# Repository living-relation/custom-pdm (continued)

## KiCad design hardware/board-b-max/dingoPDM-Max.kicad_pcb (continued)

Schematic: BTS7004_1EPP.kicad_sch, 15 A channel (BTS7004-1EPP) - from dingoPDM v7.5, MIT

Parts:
C47: 100nF; C_0805_2012Metric; MPN CC0805KRX7R9BB104; Digi-Key_PN 478-1395-1-ND
C51: 47nF; C_0805_2012Metric; MPN C0805C473K5RAC7800; Digi-Key_PN 399-C0805C473K5RACTUCT-ND
C55: 10nF; C_0805_2012Metric; MPN CL21B103KBANNNC; Digi-Key_PN 311-1136-1-ND
C59: 220pF; C_0805_2012Metric; MPN CC0805GRNPO0BN221; Digi-Key_PN 399-1138-1-ND
D21: 5.1V; D_SOD-323_HandSoldering; MPN PDZ5.1B,115; Digi-Key_PN 1727-5155-1-ND
D25: BYG23M; DO-214AC; MPN BYG23M-E3/TR; Digi-Key_PN BYG23M-E3/TR3GICT-ND
R56, R60, R68, R76: 4.7K; R_0805_2012Metric; MPN 0805W8F4701T5E; Digi-Key_PN 311-4.70KCRCT-ND
R64: 47R 1/4W; R_1206_3216Metric; MPN FRC1206J470 TS; Digi-Key_PN 311-47.0FRCT-ND
R72: 1.2K; R_0805_2012Metric; MPN 0805W8F1201T5E; Digi-Key_PN 311-1.20KCRCT-ND
U23: BTS7004-1EPP; TDSO-14; MPN BTS70041EPPXUMA1; LCSC C534825

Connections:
+12V: C47.2, C51.2, U23.15 (VS); also elsewhere on the board
/HighCurrentDrivers2/CH5/IS: C59.2, R68.1; also elsewhere on the board
GND: C47.1, C55.1, C59.1, D21.2 (A), D25.A, R64.1, R72.2; also elsewhere on the board
unnamed: D21.1 (K), R68.2, R76.1
unnamed: R60.1, U23.3 (DEN)
unnamed: C51.1, R64.2, U23.1 (GND)
unnamed: R56.1, U23.2 (IN)
unnamed: R72.1, R76.2, U23.4 (IS)
PF_DEN5_6: R60.2; also elsewhere on the board
PF_IN5: R56.2; also elsewhere on the board
PF_OUT5: C55.2, D25.K, U23.8 (OUT1), U23.9 (OUT2), U23.10 (OUT3), U23.11 (NC4), U23.12 (OUT4), U23.13 (OUT5), U23.14 (OUT6); also elsewhere on the board

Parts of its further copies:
C48, C49, C50: 100nF; C_0805_2012Metric; MPN CC0805KRX7R9BB104; Digi-Key_PN 478-1395-1-ND
C52, C53, C54: 47nF; C_0805_2012Metric; MPN C0805C473K5RAC7800; Digi-Key_PN 399-C0805C473K5RACTUCT-ND
C56, C57, C58: 10nF; C_0805_2012Metric; MPN CL21B103KBANNNC; Digi-Key_PN 311-1136-1-ND
C60, C61, C62: 220pF; C_0805_2012Metric; MPN CC0805GRNPO0BN221; Digi-Key_PN 399-1138-1-ND
D22, D23, D24: 5.1V; D_SOD-323_HandSoldering; MPN PDZ5.1B,115; Digi-Key_PN 1727-5155-1-ND
D26, D27, D28: BYG23M; DO-214AC; MPN BYG23M-E3/TR; Digi-Key_PN BYG23M-E3/TR3GICT-ND
R57, R58, R59, R61, R62, R63, R69, R70, R71, R77, R78, R79: 4.7K; R_0805_2012Metric; MPN 0805W8F4701T5E; Digi-Key_PN 311-4.70KCRCT-ND
R65, R66, R67: 47R 1/4W; R_1206_3216Metric; MPN FRC1206J470 TS; Digi-Key_PN 311-47.0FRCT-ND
R73, R74, R75: 1.2K; R_0805_2012Metric; MPN 0805W8F1201T5E; Digi-Key_PN 311-1.20KCRCT-ND
U24, U25, U26: BTS7004-1EPP; TDSO-14; MPN BTS70041EPPXUMA1; LCSC C534825

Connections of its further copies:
+12V: C48.2, C49.2, C50.2, C52.2, C53.2, C54.2, U24.15 (VS), U25.15 (VS), U26.15 (VS); also elsewhere on the board
/HighCurrentDrivers2/CH6/IS: C60.2, R69.1; also elsewhere on the board
/HighCurrentDrivers2/CH7/IS: C61.2, R70.1; also elsewhere on the board
/HighCurrentDrivers2/CH8/IS: C62.2, R71.1; also elsewhere on the board
GND: C48.1, C49.1, C50.1, C56.1, C57.1, C58.1, C60.1, C61.1, C62.1, D22.2 (A), D23.2 (A), D24.2 (A), D26.A, D27.A, D28.A, R65.1, R66.1, R67.1, R73.2, R74.2, R75.2; also elsewhere on the board
unnamed: D22.1 (K), R69.2, R77.1
unnamed: D23.1 (K), R70.2, R78.1
unnamed: D24.1 (K), R71.2, R79.1
unnamed: R61.1, U24.3 (DEN)
unnamed: C52.1, R65.2, U24.1 (GND)
unnamed: R57.1, U24.2 (IN)
unnamed: R73.1, R77.2, U24.4 (IS)
unnamed: R62.1, U25.3 (DEN)
unnamed: C53.1, R66.2, U25.1 (GND)
unnamed: R58.1, U25.2 (IN)
unnamed: R74.1, R78.2, U25.4 (IS)
unnamed: R63.1, U26.3 (DEN)
unnamed: C54.1, R67.2, U26.1 (GND)
unnamed: R59.1, U26.2 (IN)
unnamed: R75.1, R79.2, U26.4 (IS)
PF_DEN5_6: R61.2; also elsewhere on the board
PF_DEN7_8: R62.2, R63.2; also elsewhere on the board
PF_IN6: R57.2; also elsewhere on the board
PF_IN7: R58.2; also elsewhere on the board
PF_IN8: R59.2; also elsewhere on the board
PF_OUT6: C56.2, D26.K, U24.8 (OUT1), U24.9 (OUT2), U24.10 (OUT3), U24.11 (NC4), U24.12 (OUT4), U24.13 (OUT5), U24.14 (OUT6); also elsewhere on the board
PF_OUT7: C57.2, D27.K, U25.8 (OUT1), U25.9 (OUT2), U25.10 (OUT3), U25.11 (NC4), U25.12 (OUT4), U25.13 (OUT5), U25.14 (OUT6); also elsewhere on the board
PF_OUT8: C58.2, D28.K, U26.8 (OUT1), U26.9 (OUT2), U26.10 (OUT3), U26.11 (NC4), U26.12 (OUT4), U26.13 (OUT5), U26.14 (OUT6); also elsewhere on the board

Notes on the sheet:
RC Filter
Flyback

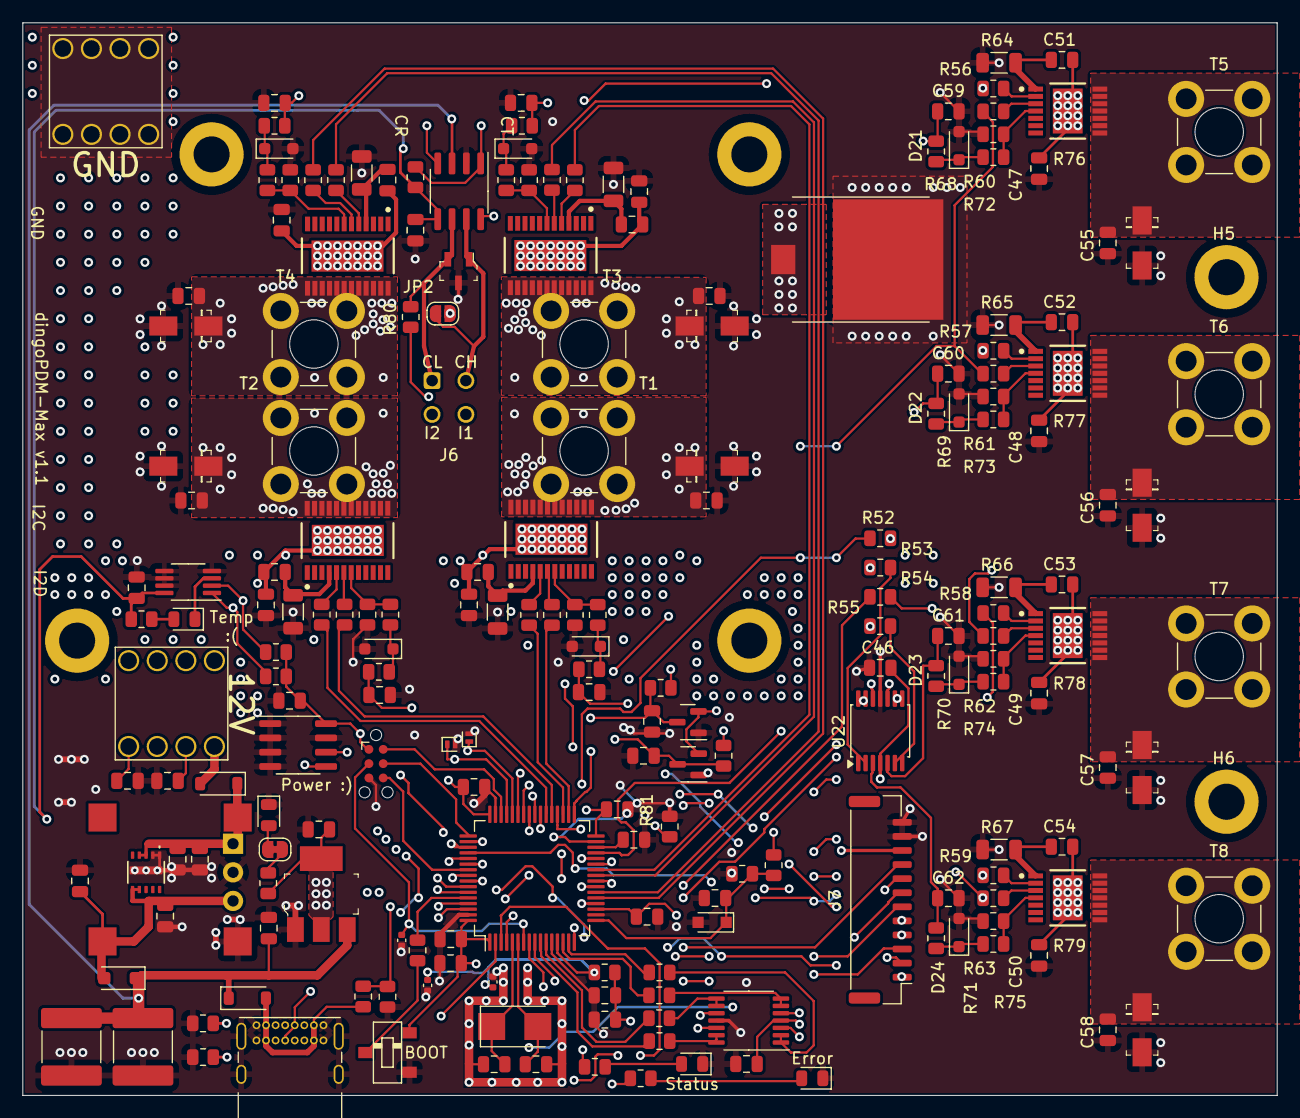
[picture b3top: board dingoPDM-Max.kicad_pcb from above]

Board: 4 copper layers, 111.4 x 95.2 mm, 211 parts (1 on the bottom side), 139 nets.

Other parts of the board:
H5, H6: M3; MountingHole_3.2mm_M3_ISO7380_Pad

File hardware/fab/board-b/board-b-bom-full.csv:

Qty,Designator,Value,Footprint,Manufacturer,MPN,LCSC,Digi-Key,Approved alternates,Fitted by
20,"C1,C2,C5,C9,C11,C12,C13,C14,C16,C18,C22,C24,C28,C32,C36,C46,C47,C48,C49,C50",100nF,C_0805_2012Metric,YAGEO,CC0805KRX7R9BB104,C49678,478-1395-1-ND,,JLCPCB SMT
3,"C3,C66,C67",4.7uF,C_0805_2012Metric,TDK,CGA4J1X7R1H475KT0Y0N,C694229,,"HRE CGA0805X7R475K500MT (4.7 uF 50 V X7R 0805, LCSC C6119944)",JLCPCB SMT
2,"C4,C68",22uF,C_0805_2012Metric,Murata,GRM21BZ71A226ME15L,C907991,,"CCTC TCC0805X7R226M100FT (22 uF 10 V X7R 0805, LCSC C53133025)",JLCPCB SMT
1,C6,10uF,C_0805_2012Metric,Samsung Electro-Mechanics,CL21B106KPQNNNE,C32635,,,JLCPCB SMT
2,"C7,C8",27pF,C_0805_2012Metric,FH (Guangdong Fenghua),0805CG270J500NT,C1808,478-10518-1-ND,,JLCPCB SMT
2,"C10,C15",4.7uF,C_0805_2012Metric,Samsung Electro-Mechanics,CL21B475KAFNNNE,C98195,,,JLCPCB SMT
2,"C17,C19",1uF,C_0805_2012Metric,Samsung Electro-Mechanics,CL21B105KBFNNNE,C28323,311-1365-1-ND,,JLCPCB SMT
10,"C20,C21,C25,C29,C33,C37,C55,C56,C57,C58",10nF,C_0805_2012Metric,Samsung Electro-Mechanics,CL21B103KBANNNC,C1710,311-1136-1-ND,,JLCPCB SMT
8,"C23,C27,C31,C35,C51,C52,C53,C54",47nF,C_0805_2012Metric,KEMET,C0805C473K5RAC7800,C3879816,399-C0805C473K5RACTUCT-ND,"KEMET C0805C473K5RACTU (same part, other reel code; DK 399-C0805C473K5RACTUCT-ND)",JLCPCB SMT
8,"C26,C30,C34,C38,C59,C60,C61,C62",220pF,C_0805_2012Metric,YAGEO,CC0805GRNPO0BN221,C576920,399-1138-1-ND,,JLCPCB SMT
2,"C39,C40",47uF,C_2220_5750Metric,PSA,FS55X476K250LRG,C22388555,445-7935-1-ND,,JLCPCB SMT
2,"C63,C65",100nF,C_0402_1005Metric,Samsung Electro-Mechanics,CL05B104KO5NNNC,C1525,,YAGEO CC0402KRX7R7BB104 (X7R 16 V 0402),JLCPCB SMT
1,C64,1uF,C_0402_1005Metric,CCTC,TCC0402X7R105K100AT,C47325373,,"YAGEO CC0402KRX7R6BB105 (X7R 10 V 0402, LCSC C7500381)",JLCPCB SMT
1,D1,3.3V,D_SOD-323_HandSoldering,Nexperia,"PDZ3.3B,115",C426855,1727-5150-1-ND,,JLCPCB SMT
1,D2,SM8S24CA,D_DO-218AB_Vishay_SM8S,Bourns,SM8S24CA-Q,C1976790,SM8S24CA-QCT-ND,"Vishay SM8S24CAHM3/I (LCSC C20036943, DK 112-SM8S24CAHM3/ITR-ND); Panjit SM8H24CAS-AU",JLCPCB SMT
2,"D3,D6",Schottky,D_SOD-123,Nexperia,PMEG10010ELRX,C179426,1727-2394-1-ND,,JLCPCB SMT
1,D4,PMEG2010AEH,D_SOD-123F,Nexperia,"PMEG2010AEH,115",C110921,"1727-PMEG2010AEH,115CT-ND",,JLCPCB SMT
1,D5,GRN,LED_0805_2012Metric,OSRAM,LG R971-KN-1-0-20-R18,C2899888,475-1410-1-ND,,do not fit
2,"D7,D10",RED,LED_0805_2012Metric,OSRAM,LS R976-NR-1-0-20-R18,C2899997,475-1278-1-ND,,JLCPCB SMT
1,D8,GRN,LED_0805_2012Metric,OSRAM,LG R971-KN-1-0-20-R18,C2899888,475-1410-1-ND,,JLCPCB SMT
1,D9,NUP2105LT1G,SOT-23-3,DOWO,NUP2105LT1G,C2976509,NUP2105LT1GOSCT-ND,onsemi NUP2105LT1G (DK NUP2105LT1GOSCT-ND),JLCPCB SMT
2,"D11,D12",BAT54S,SOT-23,Nexperia,"BAT54S,215",C47546,BAT54SLT1GOSCT-ND,onsemi BAT54SLT1G (DK BAT54SLT1GOSCT-ND),JLCPCB SMT
8,"D13,D15,D17,D19,D25,D26,D27,D28",BYG23M,DO-214AC,Vishay,BYG23M-E3/TR,C141573,BYG23M-E3/TR3GICT-ND,,JLCPCB SMT
8,"D14,D16,D18,D20,D21,D22,D23,D24",5.1V,D_SOD-323_HandSoldering,Nexperia,"PDZ5.1B,115",C85392,1727-5155-1-ND,,JLCPCB SMT
2,"D29,D30",PESD5V0F1BL,D_SOD-882,Nexperia,"PESD5V0F1BL,315",C45961,,Nexperia PESD5V0F1BLZ (LCSC C6952437); BORN PESD5V0F1BL-N (LCSC C2929237),JLCPCB SMT
1,FB1,Ferrite_Bead_Small,R_0805_2012Metric,Murata,BLM21PG221SN1D,C85840,490-1054-1-ND,,JLCPCB SMT
2,"J1,J3",RedCubeTerminal,M6_Hole_8Pin_7461084,Wurth Elektronik,7461084,C6828431,732-3203-ND,,not JLCPCB: press in after delivery (fab-notes.md)
1,J2,USB_C_Receptacle_USB2.0,USB_C_Receptacle_GCT_USB4085,GCT,USB4085-GF-A,C7095263,2073-USB4085-GF-ACT-ND,,JLCPCB THT
1,J7,INPUT BOARD B_IN3-10,JST_GH_BM12B-GHS-TBT_1x12-1MP_P1.25mm_Vertical,JST,BM12B-GHS-TBT,C20089173,455-BM12B-GHS-TBTCT-ND,,JLCPCB SMT
1,R1,47K,R_0805_2012Metric,YAGEO,RT0805DRD0747KL,C327035,311-47.0KCRCT-ND,"UNI-ROYAL 0805W8F4702T5E (1 %, LCSC C17713, basic)",JLCPCB SMT
36,"R2,R4,R15,R16,R21,R22,R25,R26,R27,R28,R31,R32,R33,R34,R37,R38,R39,R40,R43,R44,R56,R57,R58,R59,R60,R61,R62,R63,R68,R69,R70,R71,R76,R77,R78,R79",4.7K,R_0805_2012Metric,UNI-ROYAL,0805W8F4701T5E,C17673,311-4.70KCRCT-ND,,JLCPCB SMT
1,R3,120R,R_0805_2012Metric,UNI-ROYAL,0805W8F1200T5E,C17437,311-120CRCT-ND,YAGEO RC0805FR-07120RL (DK 311-120CRCT-ND),do not fit
5,"R5,R10,R12,R13,R81",10K,R_0805_2012Metric,UNI-ROYAL,0805W8F1002T5E,C17414,311-10.0KCRDKR-ND,,JLCPCB SMT
2,"R6,R7",5.1K,R_0805_2012Metric,Viking,ARG05FTC5101,C218638,311-5.1KARCT-ND,,JLCPCB SMT
12,"R8,R9,R14,R17,R18,R19,R20,R52,R53,R54,R55,R80",120R,R_0805_2012Metric,UNI-ROYAL,0805W8F1200T5E,C17437,311-120CRCT-ND,YAGEO RC0805FR-07120RL (DK 311-120CRCT-ND),JLCPCB SMT
1,R11,1K,R_0805_2012Metric,UNI-ROYAL,0805W8F1001T5E,C17513,311-1.0KARCT-ND,,JLCPCB SMT
8,"R23,R29,R35,R41,R72,R73,R74,R75",1.2K,R_0805_2012Metric,UNI-ROYAL,0805W8F1201T5E,C17379,311-1.20KCRCT-ND,YAGEO RC0805FR-071K2L (DK 311-1.20KCRCT-ND),JLCPCB SMT
8,"R24,R30,R36,R42,R64,R65,R66,R67",47R 1/4W,R_1206_3216Metric,FOJAN,FRC1206J470 TS,C2907508,311-47.0FRCT-ND,,JLCPCB SMT
1,SW1,BOOT,CJS-1200TB,Nidec Components,CJS-1200TB1,C2921631,563-CJS-1200TB1CT-ND,,JLCPCB SMT
8,"T1,T2,T3,T4,T5,T6,T7,T8",74650074R,Wuerth_REDCUBE-THR_WP-THRBU_74650074_THR,Wurth Elektronik,74650074R,(none: JLCPCB global sourcing by MPN),732-74650074RCT-ND,,JLCPCB THT
1,U1,VXO780x-500-M,VXO78x-500-M,CUI,VXO7805-500-M-TR,C5137464,102-VXO7805-500-M-CT-ND,,do not fit
1,U2,TLV1117LV33DCYR,SOT-223,Texas Instruments,TLV1117LV33DCYR,C15578,296-28778-1-ND,,JLCPCB SMT
1,U3,MCP2562FD-E/SN,SOIC-8_3.9x4.9mm_P1.27mm,Microchip,MCP2562FD-E/SN,C124016,MCP2562FD-E/SN-ND,,JLCPCB SMT
1,U4,STM32F446RET7,LQFP-64_10x10mm_P0.5mm,STMicroelectronics,STM32F446RET7,C1343794,497-16775-ND,STMicroelectronics STM32F446RET6 (s9a; LCSC C69336),JLCPCB SMT
1,U5,CY15B064J-SXE,SOIC-8_3.9x4.9mm_P1.27mm,Infineon,CY15B064J-SXE,C2953601,448-CY15B064J-SXE-ND,"RAMXEED MB85RC64TAPNF-G-AWERE2 (LCSC C43379785; 105 C part: fit only with the board's critical limit keeping the FRAM <= 105 C, docs/heat-analysis.md 5)",JLCPCB SMT
1,U6,MCP9808,MSOP-8_3x3mm_P0.65mm,Microchip,MCP9808T-E/MS,C129490,MCP9808T-E/MSCT-ND,,JLCPCB SMT
2,"U7,U22",TLV9004IPWR,TSSOP-14_4.4x5mm_P0.65mm,Texas Instruments,TLV9004IPWR,C2058050,296-51827-1-ND,"Microchip MCP6004T-E/ST (RRIO, -40 to 125 C, same TSSOP-14 pinout, DS20001733)",JLCPCB SMT
4,"U8,U9,U10,U11",BTS70012-1ESP,TSDSO-24,Infineon,BTS700121ESPXUMA1,C3232444,448-BTS700121ESPXUMA2CT-ND,Infineon BTS700121ESPXUMA2 (DK 448-BTS700121ESPXUMA2CT-ND),JLCPCB SMT
1,U12,OKI-78SR-5_1.5-W36H-C,Converter_DCDC_Murata_OKI-78SR_Horizontal,Murata,OKI-78SR-5/1.5-W36H-C,C266374,811-2692-ND,,do not fit
4,"U23,U24,U25,U26",BTS7004-1EPP,TDSO-14,Infineon,BTS70041EPPXUMA1,C534825,BTS70041EPPXUMA1CT-ND,,JLCPCB SMT
1,U27,LMZM23601V5,Texas_SIL0010A_MicroSiP-10-1EP_3.8x3mm_P0.6mm_EP0.7x2.9mm_TI,Texas Instruments,LMZM23601V5SILR,C2868357,296-LMZM23601V5SILRCT-ND,"TI LMZM23601V5SILT (same part, 250 reel, LCSC C2876787)",JLCPCB SMT
1,Y1,8MHz,Crystal_SMD_5032-2Pin_5.0x3.2mm_HandSoldering,ECS Inc.,ECS-80-18-30Q-CES-TR,(none: JLCPCB global sourcing by MPN),50-ECS-80-18-30Q-CES-TRCT-ND,"ECS ECS-80-18-30Q-VY-TR (-40..105 C, LCSC C6844210)",JLCPCB SMT

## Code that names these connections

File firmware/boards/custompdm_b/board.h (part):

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/*
 * GPIOA setup:
 *
 * PA0  - PF3_IS                    (analog in).
 * PA1  - PF4_IS                    (analog in).
 * PA2  -                           (input pullup).
 * PA3  - BATT_SENSE                (analog in).
 * PA4  -                           (input pullup).
 * PA5  - PF4_DEN                   (output pushpull pulldown).
 * PA6  - PF4_IN                    (output pushpull pulldown).
 * PA7  -                           (input pullup).
 * PA8  -                           (input pullup).
 * PA9  - USB_VBUS                  (input pulldown).
 * PA10 - DIG_IN1                   (input).
 * PA11 - USB_DM                    (alternate 10, usb dm).
 * PA12 - USB_DP                    (alternate 10, usb dp).
 * PA13 - SWDIO                     (alternate 0, swdio).
 * PA14 - SWCLK                     (alternate 0, swclk).
 * PA15 -                           (input pullup).
 */
#define VAL_GPIOA_MODER             (PIN_MODE_ANALOG(GPIOA_PIN0) |          \
                                     PIN_MODE_ANALOG(GPIOA_PIN1) |          \
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/*
 * GPIOB setup:
 *
 * PB0  - PF3_IN                    (output pushpull puLLdown).
 * PB1  -                           (input pullup).
 * PB2  -                           (input pullup).
 * PB3  - SWO                       (alternate 0, swo).
 * PB4  -                           (input pullup).
 * PB5  -                           (input pullup).
 * PB6  - I2C1_SCL                  (alternate 4, i2c scl).
 * PB7  - I2C1_SDA                  (alternate 4, i2c sda).
 * PB8  - CAN_RX                    (alternate 9, can rx).
 * PB9  - CAN_TX                    (alternate 9, can tx).
 * PB10 -                           (input pullup).
 * PB11 -                           (input pullup).
 * PB12 -                           (input pullup).
 * PB13 - PF1_DEN                   (output pushpull pulldown).
 * PB14 - PF1_IN                    (output pushpull pulldown).
 * PB15 -                           (input pullup).
 */
#define VAL_GPIOB_MODER             (PIN_MODE_OUTPUT(GPIOB_PIN0) |          \
                                     PIN_MODE_ANALOG(GPIOB_PIN1) |           \
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/*
 * GPIOC setup:
 *
 * PC0  - ERROR_LED                 (output pushpull pulldown).
 * PC1  - STATUS_LED                (output pushpull pulldown).
 * PC2  - PF2_IS                    (analog input).
 * PC3  - PF1_IS                    (analog input).
 * PC4  -                           (input pullup).
 * PC5  - PF3_DEN                   (output pushpull pulldown).
 * PC6  - PF2_DEN                   (output pushpull pulldown).
 * PC7  - PF2_IN                    (output pushpull pulldown).
 * PC8  -                           (input pullup).
 * PC9  - DIG_IN2                   (input).
 * PC10 - E1                        (output pushpull pulldown).
 * PC11 - E2                        (output pushpull pulldown).
 * PC12 - CAN_STANDBY               (output pushpull pulldown).
 * PC13 - E3                        (output pushpull pulldown).
 * PC14 -                           (input pullup).
 * PC15 -                           (input pullup).
 */
#define VAL_GPIOC_MODER             (PIN_MODE_OUTPUT(GPIOC_PIN0) |          \
                                     PIN_MODE_OUTPUT(GPIOC_PIN1) |          \
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 *
 * PD0  - PIN0                      (input pullup).
 * PD1  - PIN1                      (input pullup).
 * PD2  - PIN2                      (input pullup).
 * PD3  - PIN3                      (input pullup).
 * PD4  - PIN4                      (input pullup).
 * PD5  - PIN5                      (input pullup).
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/*
 * GPIOH setup:
 *
 * PH0  - PIN0                      (input pullup).
 * PH1  - PIN1                      (input pullup).
 * PH2  - PIN2                      (input pullup).
 * PH3  - PIN3                      (input pullup).
 * PH4  - PIN4                      (input pullup).
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
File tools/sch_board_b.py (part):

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  * HighCurrentDrivers2.kicad_sch - copy of the Max's HighCurrentDrivers page (4 channel sheets + LM324 IS buffer),
                              pointed at BTS7004_1EPP and renamed to channels 5-8. Channels 5+6 and 7+8 share a DEN pin.
  * MCU pins (were no-connect):
        PF_IN5 PA8 (TIM1_CH1)   PF_IN6 PB10 (TIM2_CH3)   PF_IN7 PA15 (TIM2_CH1)   PF_IN8 PC8 (TIM8_CH3)
        PF_DEN5_6 PB12          PF_DEN7_8 PB15
        PF_IS5 PA2 (ADC_IN2)    PF_IS6 PA4 (ADC_IN4)     PF_IS7 PA7 (ADC_IN7)     PF_IS8 PC4 (ADC_IN14)
        B_IN3..B_IN10 = PC14 PC15 PC13 PD2 PB4 PB5 PC10 PC11       B_AN = PB1 (ADC_IN9)
        (B_IN5 is on PC13, not PB2: PB2 is BOOT1, a start-up pin. Dan, 2026-11-10, B1. PB2 stays no-connect.)
  * Connectors sheet: T1-T8 = bolt-down output terminals (Wuerth REDCUBE THR M4), one per output; J4 (Deutsch DT) removed.
                      J6 = wire pads in the Micro-Fit 2x2 hole pattern (a2b, 2026-11-12): 1 CAN_L, 2 CAN_H, 3 INPUT2,
                      4 INPUT1 (order follows the old J4 track ends).
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GH12 = "Connector_JST:JST_GH_BM12B-GHS-TBT_1x12-1MP_P1.25mm_Vertical"    # top entry: sits inside the board, not at an edge

OUT_PINS = {  # net: (U4 pin name, shape)
    "PF_IN5": ("PA8", "output"), "PF_IN6": ("PB10", "output"), "PF_IN7": ("PA15", "output"), "PF_IN8": ("PC8", "output"),
    "PF_DEN5_6": ("PB12", "output"), "PF_DEN7_8": ("PB15", "output"),
    "PF_IS5": ("PA2", "input"), "PF_IS6": ("PA4", "input"), "PF_IS7": ("PA7", "input"), "PF_IS8": ("PC4", "input"),
}
IN_PINS = {"B_IN3": "PC14", "B_IN4": "PC15", "B_IN5": "PC13", "B_IN6": "PD2", "B_IN7": "PB4", "B_IN8": "PB5",
           "B_IN9": "PC10", "B_IN10": "PC11", "B_AN": "PB1"}
RENAME_HCD2 = {"PF_IN1": "PF_IN5", "PF_IN2": "PF_IN6", "PF_IN3": "PF_IN7", "PF_IN4": "PF_IN8",
               "PF_DEN1": "PF_DEN5_6", "PF_DEN2": "PF_DEN5_6", "PF_DEN3": "PF_DEN7_8", "PF_DEN4": "PF_DEN7_8",
               "PF_IS1": "PF_IS5", "PF_IS2": "PF_IS6", "PF_IS3": "PF_IS7", "PF_IS4": "PF_IS8",
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    x, y = pin_at(pin)
    t = drop_nc(t, x, y)
    items.append(glabel(net, x, y, x > X, shape))
# test points: the PC10 / PC11 / PC13 points become input labels (their wires stay), every test point is removed
TP_OF = {"PC10": "TP4", "PC11": "TP3", "PC13": "TP2"}
tp_at = {}
for s2, e2 in top_blocks(t, "symbol"):
    bb = t[s2:e2]
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wr("MCU.kicad_sch", t)

removed, dropped_labels = [], []
KEEP = set(IN_PINS)                       # our new labels sit on the PC10/PC11 test point spots
for f in sorted(glob.glob("*.kicad_sch")):
    x = rd(f)
    spots = []
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        continue
    out.append(x[pos:])
    x = "".join(out)
    # labels that only marked a test point pin (CAN_TX/RX, I2C) would dangle: drop them
    for head in ("label", "global_label"):
        out, pos = [], 0
        for s2, e2 in top_blocks(x, head):
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                pos = e2
    out.append(x[pos:])
    x = "".join(out)
    # PC13 (TP2), only when PC13 is not used as an input: remove the wire run from the test point back to the U4 pin
    # and flag the pin no-connect
    for r, p in spots:
        if r != "TP2" or f != "MCU.kicad_sch" or "PC13" in IN_PINS.values():
            continue
        ends = set(pin_end.values())
        cur, gone = p, []
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                    if abs(a[0] - cur[0]) < .01 and abs(a[1] - cur[1]) < .01:
                        hits.append(((s2, e2), b2))
            if len(hits) != 1:
                raise SystemExit(f"PC13 wire walk: {len(hits)} wires at {cur}")
            gone.append(hits[0][0])
            cur = hits[0][1]
            if any(abs(cur[0] - a) < .01 and abs(cur[1] - b2) < .01 for a, b2 in ends):
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        for s2, e2 in sorted(gone, reverse=True):
            x = x[:s2 - 2] + x[e2:]
        x = insert_items(x, [f'(no_connect\n\t\t(at {fmt(cur[0])} {fmt(cur[1])})\n\t\t(uuid "{u()}")\n\t)'])
        print("PC13 test point wiring removed:", len(gone), "wires; pin flagged no-connect at", cur)
    wr(f, x)
print("test points removed:", removed, "labels dropped:", dropped_labels)

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J4_AT = tuple(map(float, re.search(r"\(at ([\d.\-]+) ([\d.\-]+)", j4).groups()))
SHEET_PATH = re.search(r'\(path "([^"]+)"', j4).group(1)
c_glab = {re.search(r'\(global_label "([^"]+)"', t[s2:e2]).group(1): t[s2:e2] for s2, e2 in top_blocks(t, "global_label")}
tpl = c_glab["PF_OUT1"]                         # angle 180, left of the connector pins
s1, e1 = symbol_by_ref(t, "J1")
j1 = t[s1:e1]                                   # RedCube terminal symbol (1 pin), rotated 270: pin end 3.81 above the origin
if not re.search(r"\(at [\d.\-]+ [\d.\-]+ 270\)", j1):
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
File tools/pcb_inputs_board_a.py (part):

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
1. J6 placed at the left board edge (free 6.9 x 19.8 mm spot), plug opening facing the edge, linked to its
   schematic symbol (path from the netlist) so DRC schematic parity holds.
2. Pad nets from the netlist. R12 set DNP (cuts the unused IS2 buffer off PC2 / PF_IS2).
3. GND pins 11-12: short stub + via into the In1 GND plane.
4. Signals and +3V3 routed by route_board_a's A* router, preferring In2 (no planes there).
"""
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
# ---- 4. routes
R.setup(b, WIN, {"F.Cu": 1.6, "In2.Cu": 1.0, "B.Cu": 2.5})
# IN_3..IN_7 = PC10, PC11, PB4, PC13, PB3 (ex-SWO)
U4 = {f"/MCU/IN_{k}": pin for k, pin in zip(range(3, 8), ("51", "52", "56", "2", "55"))}
U4["PF_IS2"] = "10"
for num, net in list(SIG.items()) + [("9", "PF_IS2")]:
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

# ---- 5. free the spare U4 pins, step by step
# PC10, PC11, PC13 already run out to the old expansion test pads (TP8-TP10, now removed): route from those ends.
# PB3 (ex-SWO) runs out to the Tag-Connect J4: cut the last piece at J4 and route from the cut end.
# The rest fan out; a few slow-signal blockers are ripped up first and reconnected after. Plane nets (GND, +3V3,
# +12V) and the crystal are never ripped.
import pcb_rework as RW
EXISTING = ["/MCU/IN_3", "/MCU/IN_4", "/MCU/IN_6", "/MCU/IN_7"]
# Only PB4 needs a fan-out, and it escapes without ripping anything. (Experiments 2026-11-08: freeing PB5, PD2,
# PB13 or PA15 boxes in CAN_STANDBY, I2C or PF_DSEL3_4, which then can't reconnect, even with 0.6/0.3 vias.)
# Format kept for later boards: "refan" = ripped nets re-fanned first, "sides" = fan-out direction limits.
STEPS = [
    {"targets": ["/MCU/IN_5"], "rip": []},                                     # PB4
]
escape = {}
doomed = [f for f in b.GetFootprints() if f.GetReference().startswith("TP")]
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
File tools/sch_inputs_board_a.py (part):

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Run from hardware/board-a after sch_swap_board_a.py / sch_repin_board_a.py. Edits files in place.

J6 pinout (to the input daughter board):
  1-5  IN_3..IN_7 -> PC10, PC11, PB4, PC13, PB3 (5 new inputs: the most that escape U4 without disturbing dingo's
       own signals). PC10/PC11/PC13 were dingo's expansion test points E1-E3 (TP8-TP10, removed); PB3 was SWO
       (trace output, not needed to program/debug; the Tag-Connect pin is left unused); PB4 was no-connect.
  6-8  not connected (kept so one input board design also fits board B, which has more spare pins)
  9    PF2_IS (PC2, spare analog; R12 set DNP so the unused IS2 buffer no longer drives it)
  10   +3V3 (pull-up supply for the input board DIP switches)
  11-12 GND
"""
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#   ("tp", ref, name)            test point symbol -> label at its pin (the wire to U4 stays)
#   ("relabel", (x, y), name)    existing local label renamed
MCU_PINS = [
    ("tp", "TP8", "IN_3"),                        # PC10 pin 51 (was E1)
    ("tp", "TP9", "IN_4"),                        # PC11 pin 52 (was E2)
    ("nc", (127.0, 90.805), "IN_5", "R"),         # PB4  pin 56
    ("tp", "TP10", "IN_6"),                       # PC13 pin 2 (was E3)
    ("relabel", (138.43, 88.265), "IN_7"),        # PB3  pin 55 (was SWO)
]
N_IN = len(MCU_PINS)                              # J6 pins 1..N_IN carry IN_3..; the rest up to 8 are not connected
SWO_TAG_SIDE = (38.1, 172.72)                     # SWO label at the Tag-Connect (J4) -> renamed SWO_UNUSED
TESTPOINT_LIB = "Connector:TestPoint"             # every test point on every sheet is removed (Dan, 2026-11-08)
PWR_REFS = ["#PWR122", "#PWR123", "#PWR124"]

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    f'(pin "{n}"\n\t\t\t(uuid "{u()}")\n\t\t)' for n in range(1, 13)), j, count=1)
j = renew_uuids(j)
items.append(j)
items.append(f'(text "Input expansion J6 -> input daughter board (JST GH 12p).\\nIN_3..IN_7 = PC10 PC11 PB4 PC13 PB3; pins 6-8 NC.\\n'
             f'Pin 9 = PC2 spare analog (R12 DNP). Protection + pull DIPs live on the input board."\n\t\t(exclude_from_sim no)\n'
             f'\t\t(at {fmt(jx - 30.48)} {fmt(jy - 25.4)} 0)\n\t\t(effects\n\t\t\t(font\n\t\t\t\t(size 1.27 1.27)\n\t\t\t)\n'
             f'\t\t\t(justify left bottom)\n\t\t)\n\t\t(uuid "{u()}")\n\t)')

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
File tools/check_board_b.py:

"""Board B netlist checks for the channel 5-8 additions. usage: python tools/check_board_b.py <netlist.net>"""
import os
import sys

sys.path.insert(0, os.path.dirname(__file__))
import netlist_pins  # noqa: E402

d = netlist_pins.parse(sys.argv[1])
by_net = {}
for ref, rows in d.items():
    for pin, fn, net in rows:
        by_net.setdefault(net, []).append((ref, pin, fn))
pin_net = {(ref, pin): net for ref, rows in d.items() for pin, fn, net in rows}
bad = 0

# LM324 unit: (+in, -in, out)
UNITS = [("3", "2", "1"), ("5", "6", "7"), ("10", "9", "8"), ("12", "13", "14")]
for ch in range(1, 9):
    is_net = f"PF_IS{ch}"
    nodes = by_net.get(is_net, [])
    rs = [r for r, p, f in nodes if r.startswith("R")]
    mcu = [p for r, p, f in nodes if r == "U4"]
    path = "?"
    for r in rs:
        other = [pin_net[(r, p)] for p in ("1", "2") if pin_net.get((r, p)) != is_net][0]
        for ref, p, f in by_net[other]:
            for plus, minus, out in UNITS:
                if p == out and ref.startswith("U"):
                    path = f"{r} <- {ref} out{out} <- +in {pin_net[(ref, plus)]}"
    ok = mcu and path != "?" and (f"CH{ch}/" in path if ch > 4 else True)
    bad += not ok
    print(f"{is_net:8} U4 pin {mcu}  {path}  {'OK' if ok else 'CHECK'}")

for ch in range(1, 9):
    outs = sorted({r for r, p, f in by_net.get(f"PF_OUT{ch}", []) if r.startswith("U")})
    term = sorted(r for r, p, f in by_net.get(f"PF_OUT{ch}", []) if r.startswith(("T", "J")))
    ok = len(outs) == 1 and term == [f"T{ch}"]
    bad += not ok
    print(f"PF_OUT{ch}: switch {outs} terminal {term} {'OK' if ok else 'CHECK'}")
for pin, net in (("1", "CAN_L"), ("2", "CAN_H"), ("3", "INPUT2"), ("4", "INPUT1")):
    jp = sorted((r, p) for r, p, f in by_net.get(net, []) if r.startswith("J") and not r.startswith("JP"))
    ok = jp == [("J6", pin)]
    bad += not ok
    print(f"{net:8} {jp} {'OK' if ok else 'CHECK'}")
if "J4" in d:
    bad += 1
    print("J4 still present CHECK")
for net in ("PF_IN5", "PF_IN6", "PF_IN7", "PF_IN8", "PF_DEN5_6", "PF_DEN7_8"):
    sw = sorted(r for r, p, f in by_net.get(net, []) if r.startswith("U") and r != "U4")
    rr = sorted(r for r, p, f in by_net.get(net, []) if r.startswith("R"))
    mcu = [p for r, p, f in by_net.get(net, []) if r == "U4"]
    print(f"{net:10} U4 pin {mcu} parts {sorted(set(r for r, p, f in by_net.get(net, []) if r != 'U4'))}")
    bad += not mcu
# board fix: CAN terminator (C7b) and BOOT1 pull-down (B4-b(b))
term = sorted({r for r, p, f in by_net.get("CAN_H", []) + by_net.get("CAN_L", []) + by_net.get("/MCU/CAN_TERM", [])
               if r.startswith(("JP", "R"))})
ok = len(term) == 2 and len(by_net.get("/MCU/CAN_TERM", [])) == 2
bad += not ok
print(f"CAN terminator {term} {'OK' if ok else 'CHECK'}")
boot = sorted(by_net.get("/MCU/BOOT1", []))
ok = [r for r, p, f in boot if r == "U4"] == ["U4"] and any(r.startswith("R") and pin_net[(r, "1" if p == "2" else "2")] == "GND"
                                                          for r, p, f in boot)
bad += not ok
print(f"BOOT1 {boot} {'OK' if ok else 'CHECK'}")
print("FAIL" if bad else "ALL OK")
sys.exit(1 if bad else 0)

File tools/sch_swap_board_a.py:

"""Board A schematic edit: replace U8 + U9 (2x BTS7002 sheets) with one BTS7008-2EPA dual sheet.

Run from hardware/board-a. Edits files in place (git tracks the diff). Files are written with LF endings.
"""
import re, uuid

ROOT = "/8948e307-9174-4227-9c28-3ff885e6e83d"
HC = ROOT + "/00000000-0000-0000-0000-00005f54b02a"          # HighCurrentDrivers sheet path
MED = ROOT + "/00000000-0000-0000-0000-00005f54bf48"         # MedCurrentDrivers sheet path
S1 = "00000000-0000-0000-0000-00005f5a40c0"                    # sheet instance that becomes the dual
S2 = "00000000-0000-0000-0000-00005f5a40c6"                    # sheet instance to delete (old U9)
NEW_PATH = HC + "/" + S1
TEMPLATE_TAIL = "/79a0dd8b-9c30-4339-961b-e86bb429e783"         # U10 instance path tail
REFMAP = {  # U10 instance ref -> new ref
    "U10": "U8", "R34": "R13", "R35": "R14", "R36": "R20", "R37": "R19",
    "C33": "C23", "C10": "C22", "R39": "R16", "R41": "R18", "C34": "C25",
    "R38": "R15", "R40": "R17", "D13": "D9",
    "#PWR074": "#PWR055", "#PWR072": "#PWR056", "#PWR075": "#PWR057", "#PWR076": "#PWR058",
}


def rd(p):
    with open(p, encoding="utf-8", newline="") as f:
        return f.read().replace("\r\n", "\n")


def wr(p, t):
    with open(p, "w", encoding="utf-8", newline="") as f:
        f.write(t)


def block_end(t, start):
    depth, i, in_str = 0, start, False
    while i < len(t):
        c = t[i]
        if in_str:
            if c == "\\":
                i += 2
                continue
            if c == '"':
                in_str = False
        elif c == '"':
            in_str = True
        elif c == "(":
            depth += 1
        elif c == ")":
            depth -= 1
            if depth == 0:
                return i + 1
        i += 1
    raise ValueError("unbalanced")


def top_blocks(t, head):
    pat = re.compile(r"\n\t\(" + re.escape(head) + r"[\s\"]")
    return [(m.start() + 2, block_end(t, m.start() + 2)) for m in pat.finditer(t)]


def remove_block(t, pred, head):
    hits = [(s, e) for s, e in top_blocks(t, head) if pred(t[s:e])]
    if len(hits) != 1:
        raise SystemExit(f"expected 1 {head} match, got {len(hits)}")
    s, e = hits[0]
    return t[: s - 2] + t[e:]


def u():
    return str(uuid.uuid4())


# ---------- HighCurrentDrivers.kicad_sch ----------
p = "HighCurrentDrivers.kicad_sch"
t = rd(p)
t = remove_block(t, lambda b: f'(uuid "{S2}")' in b, "sheet")
t = remove_block(t, lambda b: "(xy 63.5 72.39) (xy 66.04 72.39)" in b, "wire")
t = remove_block(t, lambda b: '"Reference" "#PWR052"' in b, "symbol")


def move_label(t, name, new_at):
    blocks = [(s, e) for s, e in top_blocks(t, "global_label") if t[s:e].startswith(f'(global_label "{name}"')]
    if len(blocks) != 1:
        raise SystemExit(f"label {name}: {len(blocks)}")
    s, e = blocks[0]
    b2 = re.sub(r"\(at [\d.\-]+ [\d.\-]+ \d+\)", f"(at {new_at})", t[s:e], count=1)
    return t[:s] + b2 + t[e:]


t = move_label(t, "PF_IN2", "66.04 62.23 180")
t = move_label(t, "PF_DEN2", "66.04 58.42 180")
t = move_label(t, "PF_OUT2", "87.63 60.96 0")

# GND symbol to tie the now-unused IS2 buffer input (wire starts at 87.63 80.01)
s, e = [(s, e) for s, e in top_blocks(t, "symbol") if '"Reference" "#PWR054"' in t[s:e]][0]
g = t[s:e]
g = g.replace("(at 232.41 49.53 0)", "(at 87.63 80.01 0)")
g = re.sub(r"\(at 232\.41 ([\d.]+) 0\)", lambda m: f"(at 87.63 {float(m.group(1)) - 49.53 + 80.01:.4f} 0)", g)
g = g.replace("(at 232.537 53.9242 0)", "(at 87.757 84.4042 0)")
g = g.replace('"#PWR054"', '"#PWR061"')
g = re.sub(r'\(uuid "[^"]+"\)', lambda m: f'(uuid "{u()}")', g)
t = t[:e] + "\n\t" + g + t[e:]

# Convert sheet 1 to the dual sheet
s, e = [(s, e) for s, e in top_blocks(t, "sheet") if f'(uuid "{S1}")' in t[s:e]][0]
b = t[s:e]
for old, new in [("(size 21.59 13.97)", "(size 21.59 20.32)"),
                 ('"BTS700n_1EPP.kicad_sch"', '"BTS7008_2EPA.kicad_sch"'),
                 ("(at 66.04 59.0046 0)", "(at 66.04 65.3546 0)"),
                 ('(pin "IN" input', '(pin "IN0" input'),
                 ('(pin "OUT" output', '(pin "OUT0" output')]:
    if old not in b:
        raise SystemExit(f"sheet edit: {old} not found")
    b = b.replace(old, new)
pin_in = re.search(r'\(pin "DEN" input[\s\S]*?\n\t\t\)', b).group(0)
pin_out = re.search(r'\(pin "OUT0" output[\s\S]*?\n\t\t\)', b).group(0)


def mkpin(tmpl, old, new, old_at, new_at):
    x = tmpl.replace(f'(pin "{old}"', f'(pin "{new}"').replace(f"(at {old_at})", f"(at {new_at})")
    return re.sub(r'\(uuid "[^"]+"\)', f'(uuid "{u()}")', x, count=1)


new_pins = "\n\t\t".join([
    mkpin(pin_in, "DEN", "DSEL", "66.04 54.61 180", "66.04 58.42 180"),
    mkpin(pin_in, "DEN", "IN1", "66.04 54.61 180", "66.04 62.23 180"),
    mkpin(pin_out, "OUT0", "OUT1", "87.63 50.8 0", "87.63 60.96 0"),
])
k = b.index("\n\t\t(instances")
b = b[:k] + "\n\t\t" + new_pins + b[k:]
t = t[:s] + b + t[e:]
wr(p, t)

# ---------- rename PF_DEN2 -> PF_DSEL1_2 ----------
for f in ("HighCurrentDrivers.kicad_sch", "MCU.kicad_sch", "DingoPDM.kicad_sch"):
    x = rd(f)
    if x.count('"PF_DEN2"') == 0:
        raise SystemExit(f"no PF_DEN2 in {f}")
    wr(f, x.replace('"PF_DEN2"', '"PF_DSEL1_2"'))

# ---------- BTS7008_2EPA.kicad_sch: add instance refs for the new sheet path ----------
p = "BTS7008_2EPA.kicad_sch"
t = rd(p)
pat = re.compile(r'(\n(\t+)\(path "' + re.escape(MED + TEMPLATE_TAIL)
                 + r'"\n\t+\(reference "([^"]+)"\)\n\t+\(unit (\d+)\)\n\t+\))')
added = 0


def addinst(m):
    global added
    whole, ind, ref, unit = m.group(1), m.group(2), m.group(3), m.group(4)
    if ref not in REFMAP:
        raise SystemExit(f"no mapping for {ref}")
    added += 1
    return whole + f'\n{ind}(path "{NEW_PATH}"\n{ind}\t(reference "{REFMAP[ref]}")\n{ind}\t(unit {unit})\n{ind})'


t = pat.sub(addinst, t)
if added != len(REFMAP):
    raise SystemExit(f"added {added} instances, expected {len(REFMAP)}")
wr(p, t)
print("schematic edits OK; instances added:", added)
